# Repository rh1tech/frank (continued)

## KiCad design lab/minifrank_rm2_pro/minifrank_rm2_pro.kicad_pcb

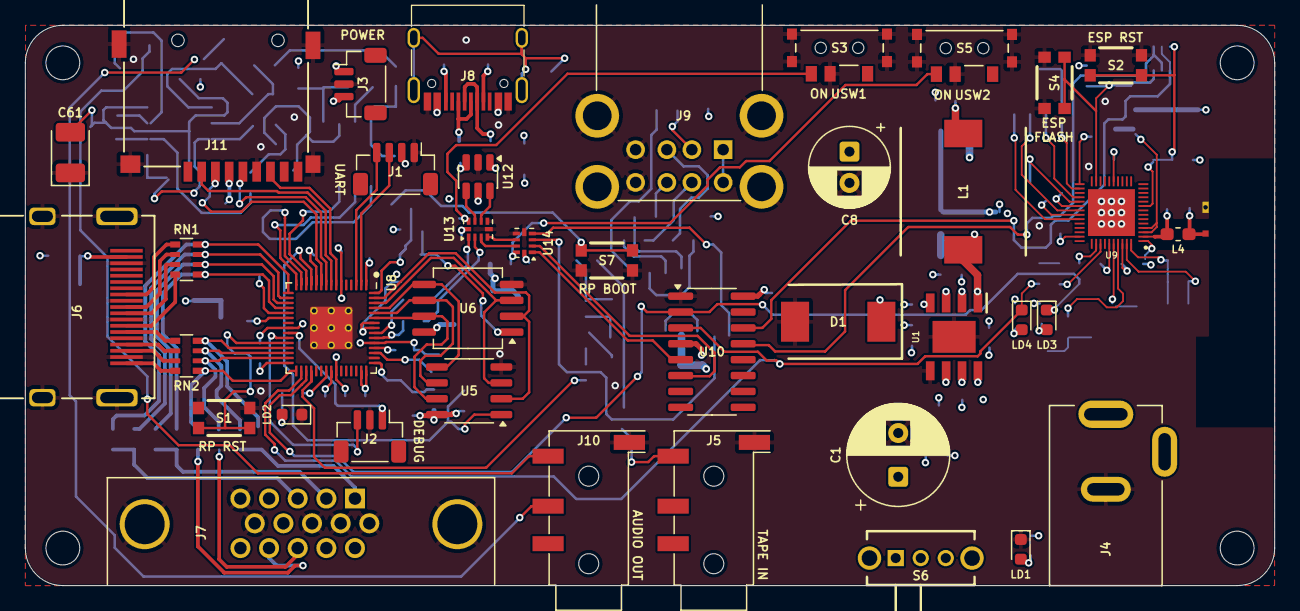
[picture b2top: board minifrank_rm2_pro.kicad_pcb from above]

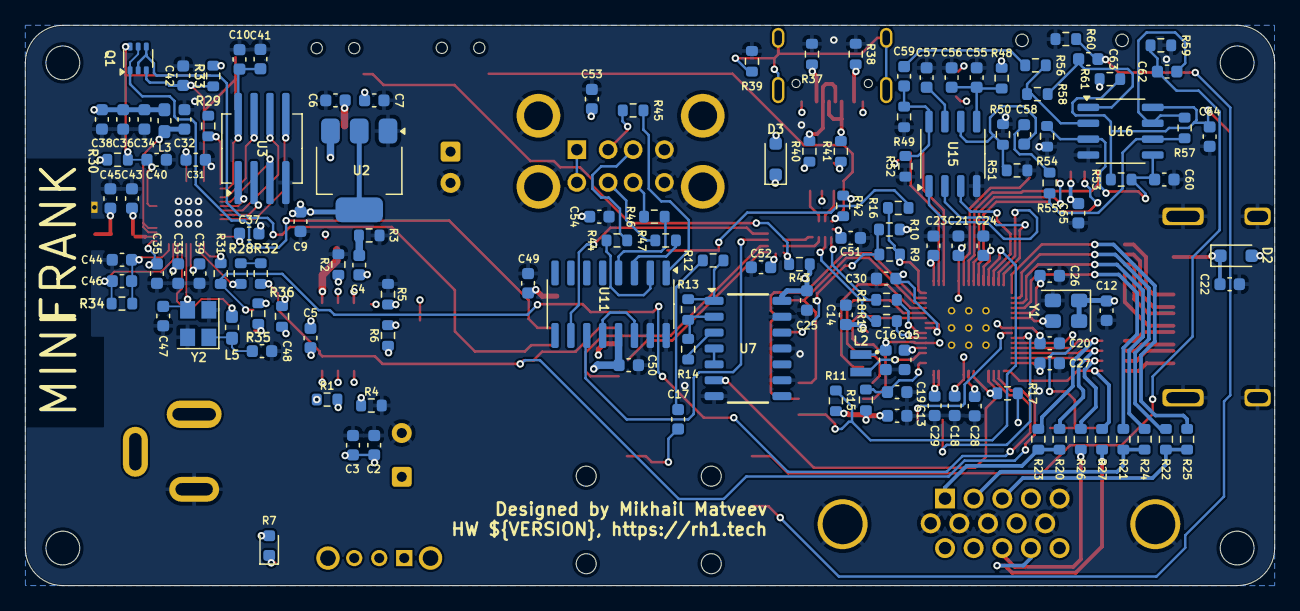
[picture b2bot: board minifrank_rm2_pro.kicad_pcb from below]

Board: 4 copper layers, 99.9 x 44.8 mm, 179 parts (135 on the bottom side), 141 nets.

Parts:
AE1: Antenna_Shield; Antenna (2.4GHz)
C1: 680u; Capacitor (Radial_D8.0mm_P3.50mm)
C2, C7, C9, C36, C53, C54, C55, C57, C58, C59, C60, C62, C63: 10u; C_0603_1608Metric
C3, C5, C6, C10, C12, C13, C14, C17, C18, C21, C22, C23, C24, C25, C26, C27, C28, C29, C30, C32, C34, C35, C37, C39, C49, C51, C52, C56, C64, C65: 100n; C_0603_1608Metric
C4: 150pF; C_0603_1608Metric
C8: 220u; Capacitor (Radial_D6.3mm_P2.50mm)
C15, C16, C19, C20, C50: 4.7u; C_0603_1608Metric
C31, C38, C41: 1u; C_0603_1608Metric
C33: 100p; C_0603_1608Metric
C40, C42: 1n; C_0603_1608Metric
C43: 1.5pF; C_0603_1608Metric
C44: 10n; C_0603_1608Metric
C45: 2.4pF; C_0603_1608Metric
C46: 3.3n; C_0603_1608Metric
C47, C48: 12p; C_0603_1608Metric
C61: 10u; Capacitor (3528, tantalum, polar)
D1: 1N5822; SS34
D2, D3: 1N5819WS; Diode (SOD-323)
H1, H2, H3, H4: Hole 2.7mm; Mounting Hole (2.7mm)
J1: UART; JST_SH_BM04B-SRSS-TB_1x04-1MP_P1.00mm_Vertical
J2: DEBUG; JST_SH_BM03B-SRSS-TB_1x03-1MP_P1.00mm_Vertical
J3: PWR; JST_SH_BM03B-SRSS-TB_1x03-1MP_P1.00mm_Vertical
J4: DC-005-5A-2.0; XKB_DC-005-5A-2.0
J5, J10: PJ-320D; Jack (3.5mm, PJ-320D)
J6: DC3RX19JA2; HDMI (female)
J7: VGA; D-SUB (15 pin, female)
J8: USB4215-03-A; USB Type C
J9: SS-52100-004; USB Type A (stacked)
J11: 104031-0811; MicroSD (SMD, long)
L1: 22uH; CDRH104RNP
L2: 3.3u; L_pol_2016
L3: 2nH; Inductor (0603 1.05x0.95)
L4: 2.7nH/0R; Inductor (0603 1.05x0.95)
L5: 24nH/0R; Inductor (0603 1.05x0.95)
LD1: Power; LED_0603_1608Metric
LD2: Blue; LED_0603_1608Metric
LD3, LD4: Orange; LED_0603_1608Metric
Q1: UMH3N; SOT-363
R1, R3, R4, R13, R14: 100K; R_0603_1608Metric
R2: 24K; R_0603_1608Metric
R5: 8.2K; R_0603_1608Metric
R6: 43K; R_0603_1608Metric
R7: 1K; LED_0603_1608Metric
R9: 0R; R_0603_1608Metric
R10, R11, R42, R43, R51, R52, R53, R54, R55, R56: 10K; R_0603_1608Metric
R12: 4.7K; R_0603_1608Metric
R15: 33R; R_0603_1608Metric
R16, R17, R23, R24, R25: 1K; R_0603_1608Metric
R18, R19: 27R; R_0603_1608Metric
R20, R21, R22: 330R; R_0603_1608Metric
R26, R27, R48, R61: 100R; R_0603_1608Metric
R28: 499R; Resistor (0603, S)
R29: 0R; Resistor (0603, S)
R30, R33: 10K; Resistor (0603, S)
R31, R32: 330R; Resistor (0603, S)
R34: 20K; Resistor (0603, S)
R35, R36: 1.5K; Resistor (0603, S)
R37, R38: 5.1K; R_0603_1608Metric
R39: 1M; R_0603_1608Metric
R40, R41, R44, R45, R46, R47: 22R; R_0603_1608Metric
R49, R50: 470R; R_0603_1608Metric
R57, R58: 47K; R_0603_1608Metric
R59, R60: 20K; R_0603_1608Metric
RN1, RN2: 270R; Resistor Array (4x0603)
S1: RP Reset; KMR_2
S2: ESP Reset; KMR_2
S3, S5: MSK12C02; SW_MSK12C02
S4: ESP Flash; KMR_2
S6: SK12D07VG3NS
S7: RP Flash; KMR_2
U1: MP1584EN-LF-Z; SOIC127P600X170-9N
U2: AMS1117 3.3; SOT-223
U3: W25Q32JVSIQ; SOIC-8 (Longer)
U5: ESP-PSRAM32; SO-8
U6: W25Q128JVS; SOIC-8
U7: CD4069UBM; SOIC127P600X175-14N
U8: RP2350; QFN 60 (RP2350A)
U9: ESP32-D0WD-V3; QFN35P500X500X90-49N-D
U10: CH340C; SOP-16
U11: MW7211A; SOP-16
U12: USBLC6-2SC6; SOT-23-6
U13, U14: TS3USB221RSER; UQFN-10
U15: TDA1387T; SO-8
U16: LM358; SO-8
Y1: ASE-12MHz; Oscillator_SMD_Abracon_ASE-4Pin_3.2x2.5mm
Y2: 40MHz; Crystal (3225)

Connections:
+1V1: C16.1, C18.1, C20.1, C21.1, L2.1, U8.6 (DVDD), U8.23 (DVDD), U8.39 (DVDD), U8.50 (VREG_FB)
+3.3VP: C32.1, L3.2, U9.3 (VDD3P3_1), U9.4 (VDD3P3_2)
+3V3: C9.1, C12.1, C13.1, C14.1, C15.1, C23.1, C24.1, C25.1, C26.1, C27.1, C28.1, C29.1, C30.1, C31.1, C33.1, C34.1, C35.1, C36.1, C37.1, C38.1, C39.1, C49.1, C51.2, C52.2, C65.2, J1.2, J3.1, J11.4 (VDD), L3.1, R7.2, R10.1, R11.2, R15.1, R30.2, R33.2, R35.2, R36.1, R42.1, R43.1, U2.2 (VO), U5.8 (VCC), U6.8 (VCC), U7.14 (VDD), U8.1 (IOVDD), U8.11 (IOVDD), U8.20 (IOVDD), U8.30 (IOVDD), U8.38 (IOVDD), U8.44 (ADC_AVDD), U8.45 (IOVDD), U8.49 (VREG_VIN), U8.53 (USB_OTP_VDD), U8.54 (QSPI_IOVDD), U9.1 (VDDA_1), U9.19 (VDD3P3_RTC), U9.37 (VDD3P3_CPU), U9.43 (VDDA_2), U9.46 (VDDA_3), U10.4 (3V), U10.16 (VCC), U13.10 (VCC), U14.10 (VCC), Y1.1 (EN), Y1.4 (Vdd)
/Audio/AMP_OUTL: C62.2, J10.T, R59.2
/Audio/AMP_OUTR: C63.2, J10.R, R60.2
/Audio/TDA_L: C58.1, R50.2, R51.1, U15.6 (A_LEFT)
/Audio/TDA_R: C59.1, R49.1, R52.1, U15.8 (A_RIGHT)
/ESP32/ANT: AE1.1 (A), C45.1, L4.1
/ESP32/CAP1: C44.1, C46.1, R34.2, U9.48 (CAP1)
/ESP32/CAP2: C46.2, R34.1, U9.47 (CAP2)
/ESP32/LNA_IN: C43.1, L4.2, U9.2 (LNA_IN)
/ESP32/U0RXD: R31.2, U9.40 (U0RXD)
/ESP32/U0TXD: R28.2, R32.2
/ESP32/XTAL_N: C47.1, U9.44 (XTAL_N), Y2.3
/ESP32/XTAL_P: L5.1, U9.45 (XTAL_P)
/ESP_CHIP_PU: C40.1, Q1.6 (C1), R30.1, S2.2, S2.4, U9.9 (CHIP_PU)
/ESP_DTR: Q1.2 (B1), Q1.4 (E2), U10.13 (DTR)
/ESP_GPIO0: C42.1, Q1.3 (C2), R33.1, S4.2, S4.4, U9.23 (GPIO0)
/ESP_RTS: Q1.1 (E1), Q1.5 (B2), U10.14 (RTS)
/ESP_RXD: LD3.1 (K), R31.1, U8.33 (GPIO21), U10.2 (TxD)
/ESP_SCK/CLK: U3.6 (CLK), U9.31 (SD_CLK)
/ESP_SCS/CMD: U3.1 (~CS), U9.30 (SD_CMD)
/ESP_SDI/SD1: U3.5 (DI(IO0)), U9.33 (SD_DATA_1)
/ESP_SDO/SD0: U3.2 (DO(IO1)), U9.32 (SD_DATA_0)
/ESP_SHD/SD2: U3.7 (IO3), U9.28 (SD_DATA_2)
/ESP_SWP/SD3: U3.3 (IO2), U9.29 (SD_DATA_3)
/ESP_TXD: LD4.1 (K), R32.1, U8.32 (GPIO20), U10.3 (RxD)
/GPIO0: J1.3, U8.2 (GPIO0)
/GPIO1: J1.4, U8.3 (GPIO1)
/GPIO4: J11.7 (DAT0), U8.7 (GPIO4)
/GPIO5: J11.2 (DAT3/CD), U8.8 (GPIO5)
/GPIO6: J11.5 (CLK), U8.9 (GPIO6)
/GPIO7: J11.3 (CMD), U8.10 (GPIO7)
/GPIO8: R11.1, U5.1 (~CE), U8.12 (GPIO8)
/GPIO9: U8.13 (GPIO9), U15.3 (DATA)
/GPIO10: U8.14 (GPIO10), U15.1 (SCLK)
/GPIO11: U8.15 (GPIO11), U15.2 (LRCK)
/GPIO12: R25.1, RN1.4 (R4.1), U8.16 (GPIO12)
/GPIO13: R22.1, RN1.3 (R3.1), U8.17 (GPIO13)
/GPIO14: R24.1, RN1.2 (R2.1), U8.18 (GPIO14)
/GPIO15: R21.1, RN1.1 (R1.1), U8.19 (GPIO15)
/GPIO16: R23.1, RN2.4 (R4.1), U8.27 (GPIO16)
/GPIO17: R20.1, RN2.3 (R3.1), U8.28 (GPIO17)
/GPIO18: R26.2, RN2.2 (R2.1), U8.29 (GPIO18)
/GPIO19: R27.2, RN2.1 (R1.1), U8.31 (GPIO19)
/GPIO22: U7.6 (I=*C), U8.34 (GPIO22)
/Power/VBUS_CON: J4.1, S6.2
/Power/VBUS_IN: C1.1, C2.1, C3.1, R1.2, S6.1, U1.7 (VIN)
/RP2350A/FLASH_SS: R9.2, R10.2, U6.1 (~CS)
/RP2350A/QSPI_SCLK: U5.6 (SCLK), U6.6 (CLK), U8.56 (QSPI_SCLK)
/RP2350A/QSPI_SD0: U5.5 (SI/SIO), U6.5 (DI(IO0)), U8.57 (QSPI_SD0)
/RP2350A/QSPI_SD1: U5.2 (SO/SIO), U6.2 (DO(IO1)), U8.59 (QSPI_SD1)
/RP2350A/QSPI_SD2: U5.3 (SIO2), U6.3 (IO2), U8.58 (QSPI_SD2)
/RP2350A/QSPI_SD3: U5.7 (SIO3), U6.7 (IO3), U8.55 (QSPI_SD3)
/RP2350A/QSPI_SS: R9.1, R16.1, U8.60 (QSPI_SS)
/RP2350A/VREG_AVDD: C19.1, R15.2, U8.46 (VREG_AVDD)
/RP2350A/VREG_LX: L2.2, U8.48 (VREG_LX)
/RP2350A/XIN: U8.21 (XIN), Y1.3 (OUT)
/RP2350A/~USB_BOOT: R16.2, S7.2, S7.4
/RP_D+: R18.1, U13.1 (1D+)
/RP_D-: R19.1, U13.2 (1D-)
/RUN: S1.2, S1.4, U8.26 (RUN)
/SWCLK: J2.1, U8.24 (SWCLK)
/SWD: J2.3, U8.25 (SWD)
/Tape In/TAPE: C17.2, J5.T
/UC_D+: U12.4 (I/O2), U13.8 (D+)
/UC_D-: U12.6 (I/O1), U13.7 (D-)
/UH_D+: U11.11 (DPU), U14.3 (2D+)
/UH_D-: U11.10 (DMU), U14.4 (2D-)
/USB Multiplexers/M1D2+: U13.3 (2D+), U14.8 (D+)
/USB Multiplexers/M1D2-: U13.4 (2D-), U14.7 (D-)
/USB/DS1+: R44.1, U11.2 (DP0)
/USB/DS1-: R45.1, U11.1 (DM0)
/USB/DS2+: R46.1, U11.4 (DP1)
/USB/DS2-: R47.1, U11.3 (DM1)
/USW1: R42.2, S3.3, U13.9 (S)
/USW2: R43.2, S5.3, U14.9 (S)
/UT_D+: U10.5 (D+), U14.1 (1D+)
/UT_D-: U10.6 (D-), U14.2 (1D-)
/VDD_SDIO: C10.1, C41.1, U3.8 (VCC), U9.26 (VDD_SDIO)
GND: AE1.2 (Shield), C1.2, C2.2, C3.2, C6.1, C7.2, C8.2, C9.2, C10.2, C12.2, C13.2, C14.2, C15.2, C16.2, C18.2, C19.2, C20.2, C21.2, C22.2, C23.2, C24.2, C25.2, C26.2, C27.2, C28.2, C29.2, C30.2, C31.2, C32.2, C33.2, C34.2, C35.2, C36.2, C37.2, C38.2, C39.2, C40.2, C41.2, C42.2, C43.2, C44.2, C45.2, C47.2, C48.2, C49.2, C50.2, C51.1, C52.1, C53.2, C54.2, C55.2, C56.2, C57.2, C60.1, C61.1, C64.1, C65.1, D1.2 (A), J1.1, J2.2, J3.2, J4.2, J5.S, J6.2 (G_D2), J6.5 (G_D1), J6.8 (G_D0), J6.11 (G_CLK), J6.17 (G_DDC/CEC), J6.20 (SHIELD1), J6.21 (SHIELD2), J6.22 (SHIELD3), J6.23 (SHIELD4), J7.0, J7.5, J7.6, J7.7, J7.8, J7.10, J8.1 (GND), J8.12 (GND), J9.4 (GND1), J9.8 (GND2), J9.9 (Shield), J10.S, J11.6 (VSS), LD1.1 (K), LD2.1 (K), R2.2, R3.2, R4.2, R5.1, R37.1, R38.1, R39.2, R49.2, R50.1, R51.2, R52.2, R54.1, R59.1, R60.1, S1.1, S1.3, S2.1, S2.3, S3.2, S3.4_1 (GND), S3.4_2 (GND), S3.4_3 (GND), S3.4_4 (GND), S4.1, S4.3, S5.2, S5.4_1 (GND), S5.4_2 (GND), S5.4_3 (GND), S5.4_4 (GND), S7.1, S7.3, U1.5 (GND), U1.9 (EP), U2.1 (GND), U3.4 (GND), U5.4 (VSS), U6.4 (GND), U7.7 (VSS), U7.9 (D14), U7.11 (E), U7.13 (F), U8.47 (VREG_PGND), U8.61 (GND), U9.49 (GND), U10.1 (GND), U11.15 (GND), U11.16 (GND), U12.2 (GND), U13.5 (GND), U13.6 (~OE), U14.5 (GND), U14.6 (~OE), U15.4 (AGND), U16.4 (V-), Y1.2 (GND), Y2.2 (G), Y2.4 (G)
GPIO25: R17.2, U8.37 (GPIO25)
unnamed: C4.2, R3.1
unnamed: C17.1, R12.2
unnamed: C48.1, L5.2, Y2.1
unnamed: C58.2, R55.2
unnamed: C59.2, R56.2
unnamed: C62.1, R57.1, U16.7
unnamed: C63.1, R58.1, U16.1
unnamed: C5.2, D1.1 (K), L1.1, U1.1 (SW)
unnamed: C22.1, D2.1 (K), J6.18 (+5V)
unnamed: D3.2 (A), J8.2 (VBUS), J8.11 (VBUS)
unnamed: J6.12 (CLKN), RN1.5 (R4.2)
unnamed: J6.10 (CLKP), RN1.6 (R3.2)
unnamed: J6.9 (D0N), RN1.7 (R2.2)
unnamed: J6.7 (D0P), RN1.8 (R1.2)
unnamed: J6.6 (D1N), RN2.5 (R4.2)
unnamed: J6.4 (D1P), RN2.6 (R3.2)
unnamed: J6.3 (D2N), RN2.7 (R2.2)
unnamed: J6.1 (D2P), RN2.8 (R1.2)
unnamed: J7.1, R20.2, R23.2
unnamed: J7.2, R21.2, R24.2
unnamed: J7.3, R22.2, R25.2
unnamed: J7.13, R26.1
unnamed: J7.14, R27.1
unnamed: J8.4 (CC1), R37.2
unnamed: J8.10 (CC2), R38.2
unnamed: J8.5 (DN2), J8.7 (DN1), R40.2
unnamed: J8.6 (DP1), J8.8 (DP2), R41.2
unnamed: J8.13 (SHIELD), R39.1
unnamed: J9.3 (D1+), R44.2
unnamed: J9.2 (D1-), R45.2
unnamed: J9.7 (D2+), R46.2
unnamed: J9.6 (D2-), R47.2
unnamed: LD1.2 (A), R7.1
unnamed: LD2.2 (A), R17.1
unnamed: LD3.2 (A), R35.1
unnamed: LD4.2 (A), R36.2
unnamed: R40.1, U12.1 (I/O1)
unnamed: R41.1, U12.3 (I/O2)
unnamed: C5.1, U1.8 (BST)
unnamed: C4.1, U1.3 (COMP)
unnamed: R1.1, R2.1, U1.2 (EN)
unnamed: R5.2, R6.2, U1.4 (FB)
unnamed: R4.1, U1.6 (FREQ)
unnamed: R12.1, R13.2, U7.1 (A)
unnamed: R14.1, U7.3 (B)
unnamed: U7.4 (H=*B), U7.5 (C)
unnamed: R13.1, R14.2, U7.2 (G-*A)
unnamed: R19.2, U8.51 (USB_DM)
unnamed: R18.2, U8.52 (USB_DP)
unnamed: R29.1, U9.25 (GPIO16)
unnamed: R28.1, U9.41 (U0TXD)
unnamed: U11.12 (VD33), U11.14 (VD3)
unnamed: C57.1, U15.7 (FLT)
unnamed: C55.1, C56.1, R48.1, U15.5 (VA)
unnamed: C60.2, R53.1, R54.2, U16.3 (+), U16.5 (+)
unnamed: R56.1, R58.2, U16.2 (-)
unnamed: R55.1, R57.2, U16.6 (-)
unnamed: C61.2, C64.2, R53.2, R61.2, U16.8 (V+)
VBUS: C6.2, C7.1, C8.1, C50.1, C53.1, C54.1, D2.2 (A), D3.1 (K), J3.3, J9.1 (VBUS1), J9.5 (VBUS2), L1.2, R6.1, R48.2, R61.1, U2.3 (VI), U11.13 (VDD5), U12.5 (VBUS)

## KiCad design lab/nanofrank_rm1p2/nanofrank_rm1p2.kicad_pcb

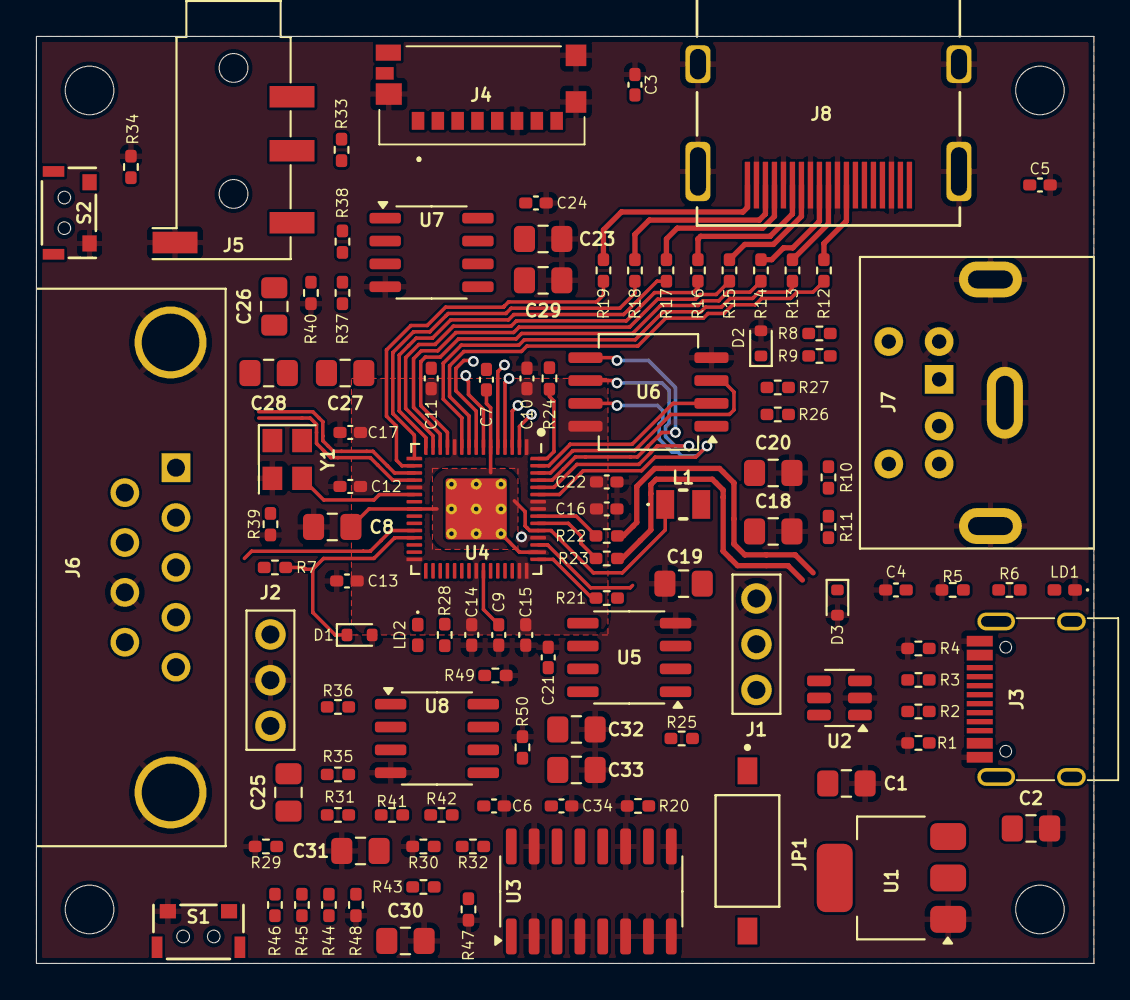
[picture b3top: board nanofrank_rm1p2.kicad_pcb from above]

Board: 4 copper layers, 58.8 x 51.5 mm, 114 parts (0 on the bottom side), 83 nets.

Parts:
C1, C2, C23, C25, C26, C27, C28, C29, C32, C33: 10u; Capacitor (0805)
C3, C4, C5, C6, C7, C9, C10, C11, C12, C13, C14, C15, C16, C17, C21, C22, C24, C34: 100n; Capacitor (0402)
C8, C18, C19, C20: 4.7u; Capacitor (0805)
C30, C31: 47n; Capacitor (0805)
D1, D2, D3: 3V3; Diode (SOD-523)
H1, H2, H3, H4: MountingHole; Mounting Hole (2.7mm)
J1: UART; Pin Header (1x03)
J2: PWR; Pin Header (1x03)
J3: USB4215-03-A; USB Type C
J4: 0475710001; MicroSD (SMD, short)
J5: PJ-320D; Jack (3.5mm, PJ-320D)
J6: D-SUB 9 Male; D-SUB (9 pin, male, top mount)
J7: MDC-036; MiniDIN (6 Pin, female)
J8: DC3RX19JA2; HDMI (female)
JP1: Main Jumpers; SW_DS04-254-2-01BK-SMT
L1: 3.3u; Inductor (0806)
LD1: Power; LED (0402)
LD2: Blue; LED (0402)
R1, R4: 5.1K; Resistor (0402)
R2, R3: 22R; Resistor (0402)
R5: 1M; Resistor (0402)
R6, R7, R8, R11, R24, R28, R45, R46: 1K; Resistor (0402)
R9, R10: 100R; Resistor (0402)
R12, R13, R14, R15, R16, R17, R18, R19: 270R; Resistor (0402)
R20, R25, R26, R31, R32, R33, R35, R37, R40, R43, R44: 10K; Resistor (0402)
R21: 33R; Resistor (0402)
R22, R23: 27R; Resistor (0402)
R27: 0R; Resistor (0402)
R29, R30, R41, R42, R47, R48: 2K; Resistor (0402)
R34, R39: 20K; Resistor (0402)
R36, R38: 47K; Resistor (0402)
R49, R50: 470R; Resistor (0402)
S1: Reset; TACT-SIDE-4623
S2: TS-1233; TACT-SIDE-4623
U1: NCP1117 3.3; SOT-223
U2: USBLC6-2SC6; SOT-23-6
U3: 74HC4052D; SOP-16
U4: RP2350; QFN 60 (RP2350A)
U5: ESP-PSRAM32; SO-8
U6: W25Q128JVS; SOIC-8
U7: LM358; SO-8
U8: TDA1387T; SO-8
Y1: ASE-12MHz; Crystal (3225, active)

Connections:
+1V1: C7.1, C8.1, C9.1, C20.1, L1.1, U4.6 (DVDD), U4.23 (DVDD), U4.39 (DVDD), U4.50 (VREG_FB)
+3V3: C1.1, C3.2, C6.2, C10.1, C11.1, C12.1, C13.1, C14.1, C15.1, C16.1, C17.1, C19.1, C21.1, C22.1, J2.1, J4.P4 (VDD), JP1.2, R6.2, R21.1, R25.2, R26.1, U1.2 (VO), U3.16 (VCC), U4.1 (IOVDD), U4.11 (IOVDD), U4.20 (IOVDD), U4.30 (IOVDD), U4.38 (IOVDD), U4.44 (ADC_AVDD), U4.45 (IOVDD), U4.49 (VREG_VIN), U4.53 (USB_OTP_VDD), U4.54 (QSPI_IOVDD), U5.8 (VCC), U6.8 (VCC), Y1.1 (EN), Y1.4 (Vdd)
/AMP_IN_L: C25.1, R31.1, U3.13 (1Z)
/AMP_IN_R: C27.1, R32.1, U3.3 (2Z)
/AUDIOSW: JP1.1, R20.2, U3.10 (S0)
/Audio Out/AMP_OUTL: C26.2, J5.T, R34.2
/Audio Out/AMP_OUTR: C28.2, J5.R, R39.2
/GPIO0: D2.1 (K), J1.2, R9.2, U4.2 (GPIO0)
/GPIO1: D3.1 (K), J1.3, R10.2, U4.3 (GPIO1)
/GPIO2: J4.P5 (CLK), U4.4 (GPIO2)
/GPIO3: J4.P3 (CMD), U4.5 (GPIO3)
/GPIO4: J4.P7 (DAT0), U4.7 (GPIO4)
/GPIO5: J4.P2 (CD/DAT3), U4.8 (GPIO5)
/GPIO6: R12.2, U4.9 (GPIO6)
/GPIO7: R13.2, U4.10 (GPIO7)
/GPIO8: R14.2, U4.12 (GPIO8)
/GPIO9: R15.2, U4.13 (GPIO9)
/GPIO10: R16.2, U4.14 (GPIO10)
/GPIO11: R17.2, U4.15 (GPIO11)
/GPIO12: R18.2, U4.16 (GPIO12)
/GPIO13: R19.2, U4.17 (GPIO13)
/GPIO14: J6.4, U4.18 (GPIO14)
/GPIO15: J6.3, U4.19 (GPIO15)
/GPIO16: D1.1 (K), R7.1, U4.27 (GPIO16)
/GPIO19: R25.1, U4.31 (GPIO19), U5.1 (~CE)
/GPIO26: R46.2, U4.40 (GPIO26_ADC0), U8.3 (DATA)
/GPIO27: R45.2, U4.41 (GPIO27_ADC1), U8.1 (SCLK)
/GPIO28: R41.1, R42.1, U4.42 (GPIO28_ADC2), U8.2 (LRCK)
/KB_CLK: J7.5, R8.2, R9.1
/KB_DATA: J7.1, R10.1, R11.2
/PWM_OUT_L: R44.2, R48.1, U3.12 (1Y0)
/PWM_OUT_R: R43.2, R47.1, U3.1 (2Y0)
/PW_D+: R22.1, U2.4 (I/O2)
/PW_D-: R23.1, U2.6 (I/O1)
/RP2350A/FLASH_SS: R26.2, R27.2, U6.1 (~CS)
/RP2350A/QSPI_SCLK: U4.56 (QSPI_SCLK), U5.6 (SCLK), U6.6 (CLK)
/RP2350A/QSPI_SD0: U4.57 (QSPI_SD0), U5.5 (SI/SIO), U6.5 (DI(IO0))
/RP2350A/QSPI_SD1: U4.59 (QSPI_SD1), U5.2 (SO/SIO), U6.2 (DO(IO1))
/RP2350A/QSPI_SD2: U4.58 (QSPI_SD2), U5.3 (SIO2), U6.3 (IO2)
/RP2350A/QSPI_SD3: U4.55 (QSPI_SD3), U5.7 (SIO3), U6.7 (IO3)
/RP2350A/QSPI_SS: R24.1, R27.1, U4.60 (QSPI_SS)
/RP2350A/VREG_AVDD: C18.1, R21.2, U4.46 (VREG_AVDD)
/RP2350A/VREG_LX: L1.2, U4.48 (VREG_LX)
/RP2350A/XIN: U4.21 (XIN), Y1.3 (OUT)
/RP2350A/~USB_BOOT: R24.2, S2.2
/RUN: S1.1, U4.26 (RUN)
/TDA_L: R50.2, U3.14 (1Y1), U8.6 (A_LEFT)
/TDA_R: R49.1, U3.5 (2Y1), U8.8 (A_RIGHT)
GND: C1.2, C2.2, C3.1, C4.2, C5.2, C6.1, C7.2, C8.2, C9.2, C10.2, C11.2, C12.2, C13.2, C14.2, C15.2, C16.2, C17.2, C18.2, C19.2, C20.2, C21.2, C22.2, C23.1, C24.1, C29.1, C30.2, C31.2, C32.2, C33.2, C34.2, D1.2 (A), D2.2 (A), D3.2 (A), J1.1, J2.2, J3.1 (GND), J3.12 (GND), J4.G1 (GND_1), J4.G2 (GND_2), J4.G3 (GND_3), J4.P6 (VSS), J5.S, J6.8, J7.3, J8.2 (G_D2), J8.5 (G_D1), J8.8 (G_D0), J8.11 (G_CLK), J8.17 (G_DDC/CEC), J8.20 (SHIELD1), J8.21 (SHIELD2), J8.22 (SHIELD3), J8.23 (SHIELD4), LD1.1 (K), LD2.1 (K), R1.1, R4.1, R5.2, R20.1, R29.2, R30.2, R34.1, R39.1, R40.1, R47.2, R48.2, R49.2, R50.1, S1.2, S2.1, U1.1 (GND), U2.2 (GND), U3.2 (2Y2), U3.4 (2Y3), U3.6 (~E), U3.7 (VEE), U3.8 (GND), U3.9 (S1), U3.11 (1Y3), U3.15 (1Y2), U4.47 (VREG_PGND), U4.61 (GND), U5.4 (VSS), U6.4 (GND), U7.4 (V-), U8.4 (AGND), Y1.2 (GND)
GPIO25: R28.2, U4.37 (GPIO25)
unnamed: C25.2, R35.2
unnamed: C26.1, R36.1, U7.7
unnamed: C27.2, R37.2
unnamed: C28.1, R38.1, U7.1
unnamed: C30.1, R41.2, R43.1, R46.1
unnamed: C31.1, R42.2, R44.1, R45.1
unnamed: J3.4 (CC1), R1.2
unnamed: J3.10 (CC2), R4.2
unnamed: J3.5 (DN2), J3.7 (DN1), R2.2
unnamed: J3.6 (DP1), J3.8 (DP2), R3.2
unnamed: J3.13 (SHIELD), R5.1
unnamed: J6.2, R7.2
unnamed: J8.12 (CLKN), R12.1
unnamed: J8.10 (CLKP), R13.1
unnamed: J8.9 (D0N), R14.1
unnamed: J8.7 (D0P), R15.1
unnamed: J8.6 (D1N), R16.1
unnamed: J8.4 (D1P), R17.1
unnamed: J8.3 (D2N), R18.1
unnamed: J8.1 (D2P), R19.1
unnamed: LD1.2 (A), R6.1
unnamed: LD2.2 (A), R28.1
unnamed: R2.1, U2.1 (I/O1)
unnamed: R3.1, U2.3 (I/O2)
unnamed: R29.1, R31.2
unnamed: R30.1, R32.2
unnamed: R23.2, U4.51 (USB_DM)
unnamed: R22.2, U4.52 (USB_DP)
unnamed: C29.2, R33.1, R40.2, U7.3 (+), U7.5 (+)
unnamed: R37.1, R38.2, U7.2 (-)
unnamed: R35.1, R36.2, U7.6 (-)
unnamed: C32.1, U8.7 (FLT)
VBUS: C2.1, C4.1, C5.1, C23.2, C24.2, C33.1, C34.1, J2.3, J3.2 (VBUS), J3.11 (VBUS), J6.6, J7.4, J8.18 (+5V), R8.1, R11.1, R33.2, U1.3 (VI), U2.5 (VBUS), U7.8 (V+), U8.5 (VA)

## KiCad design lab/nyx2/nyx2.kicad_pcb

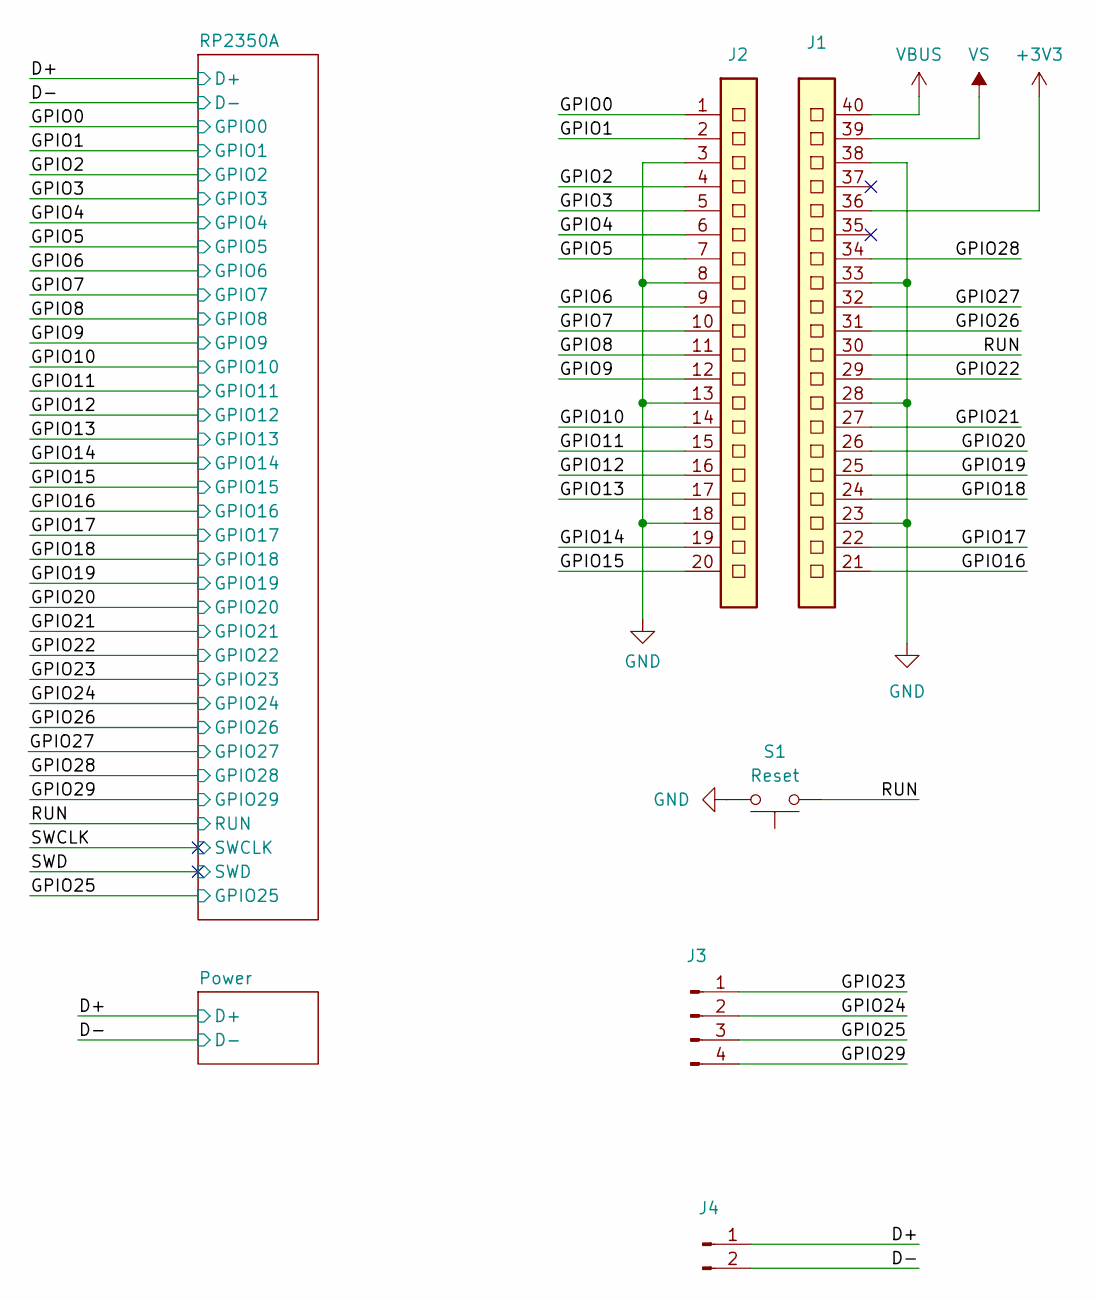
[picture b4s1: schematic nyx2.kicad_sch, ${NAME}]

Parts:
J1: CON_PICO_21-40
J2: CON_PICO_1-20
J3: Test Points (1mm x 5)
J4: Test Points (1mm x 2)
S1: Reset; Button (SMD, 3x3mm, 1-1)

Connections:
+3V3: J1.36; also elsewhere on the board
/D+: J4.1; also elsewhere on the board
/D-: J4.2; also elsewhere on the board
/GPIO0: J2.1; also elsewhere on the board
/GPIO1: J2.2; also elsewhere on the board
/GPIO2: J2.4; also elsewhere on the board
/GPIO3: J2.5; also elsewhere on the board
/GPIO4: J2.6; also elsewhere on the board
/GPIO5: J2.7; also elsewhere on the board
/GPIO6: J2.9; also elsewhere on the board
/GPIO7: J2.10; also elsewhere on the board
/GPIO8: J2.11; also elsewhere on the board
/GPIO9: J2.12; also elsewhere on the board
/GPIO10: J2.14; also elsewhere on the board
/GPIO11: J2.15; also elsewhere on the board
/GPIO12: J2.16; also elsewhere on the board
/GPIO13: J2.17; also elsewhere on the board
/GPIO14: J2.19; also elsewhere on the board
/GPIO15: J2.20; also elsewhere on the board
/GPIO16: J1.21; also elsewhere on the board
/GPIO17: J1.22; also elsewhere on the board
/GPIO18: J1.24; also elsewhere on the board
/GPIO19: J1.25; also elsewhere on the board
/GPIO20: J1.26; also elsewhere on the board
/GPIO21: J1.27; also elsewhere on the board
/GPIO22: J1.29; also elsewhere on the board
/GPIO23: J3.1; also elsewhere on the board
/GPIO24: J3.2; also elsewhere on the board
/GPIO26: J1.31; also elsewhere on the board
/GPIO27: J1.32; also elsewhere on the board
/GPIO28: J1.34; also elsewhere on the board
/GPIO29: J3.4; also elsewhere on the board
/RUN: J1.30, S1.1; also elsewhere on the board
GND: J1.23, J1.28, J1.33, J1.38, J2.3, J2.8, J2.13, J2.18, S1.2; also elsewhere on the board
GPIO25: J3.3; also elsewhere on the board
VBUS: J1.40; also elsewhere on the board
VS: J1.39

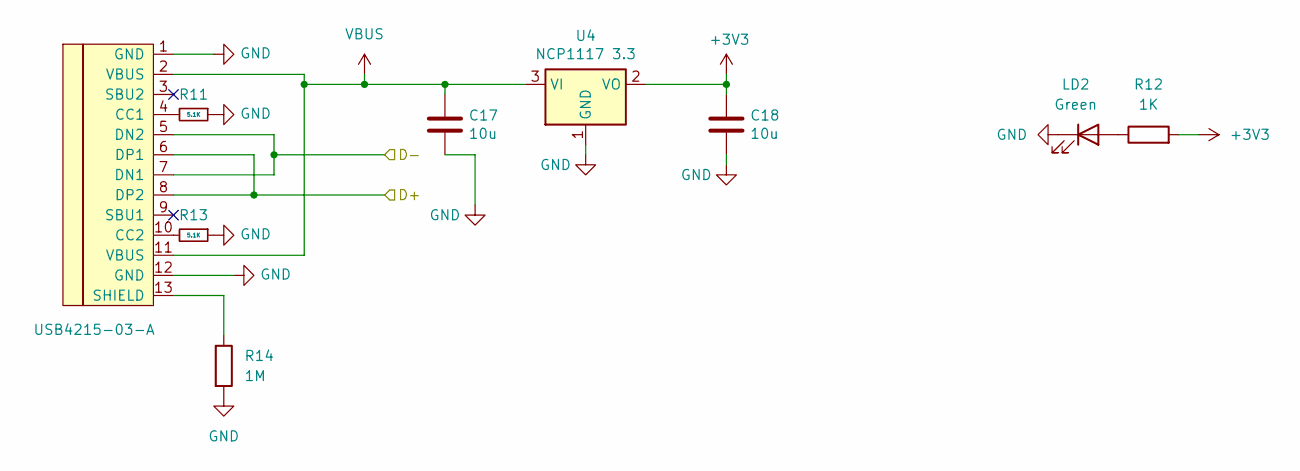
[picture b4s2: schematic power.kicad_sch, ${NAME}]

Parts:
C17, C18: 10u; Capacitor (0805)
J5: USB4215-03-A; USB Type C
LD2: Green; LED (0402)
R11, R13: 5.1K; Resistor (0402)
R12: 1K; Resistor (0402)
R14: 1M; Resistor (0402)
U4: NCP1117 3.3; SOT-223

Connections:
+3V3: C18.1, R12.2, U4.2 (VO); also elsewhere on the board
/D+: J5.6 (DP1), J5.8 (DP2); also elsewhere on the board
/D-: J5.5 (DN2), J5.7 (DN1); also elsewhere on the board
GND: C17.2, C18.2, J5.1 (GND), J5.12 (GND), LD2.1 (K), R11.1, R13.1, R14.2, U4.1 (GND); also elsewhere on the board
unnamed: J5.4 (CC1), R11.2
unnamed: J5.10 (CC2), R13.2
unnamed: J5.13 (SHIELD), R14.1
unnamed: LD2.2 (A), R12.1
VBUS: C17.1, J5.2 (VBUS), J5.11 (VBUS), U4.3 (VI); also elsewhere on the board

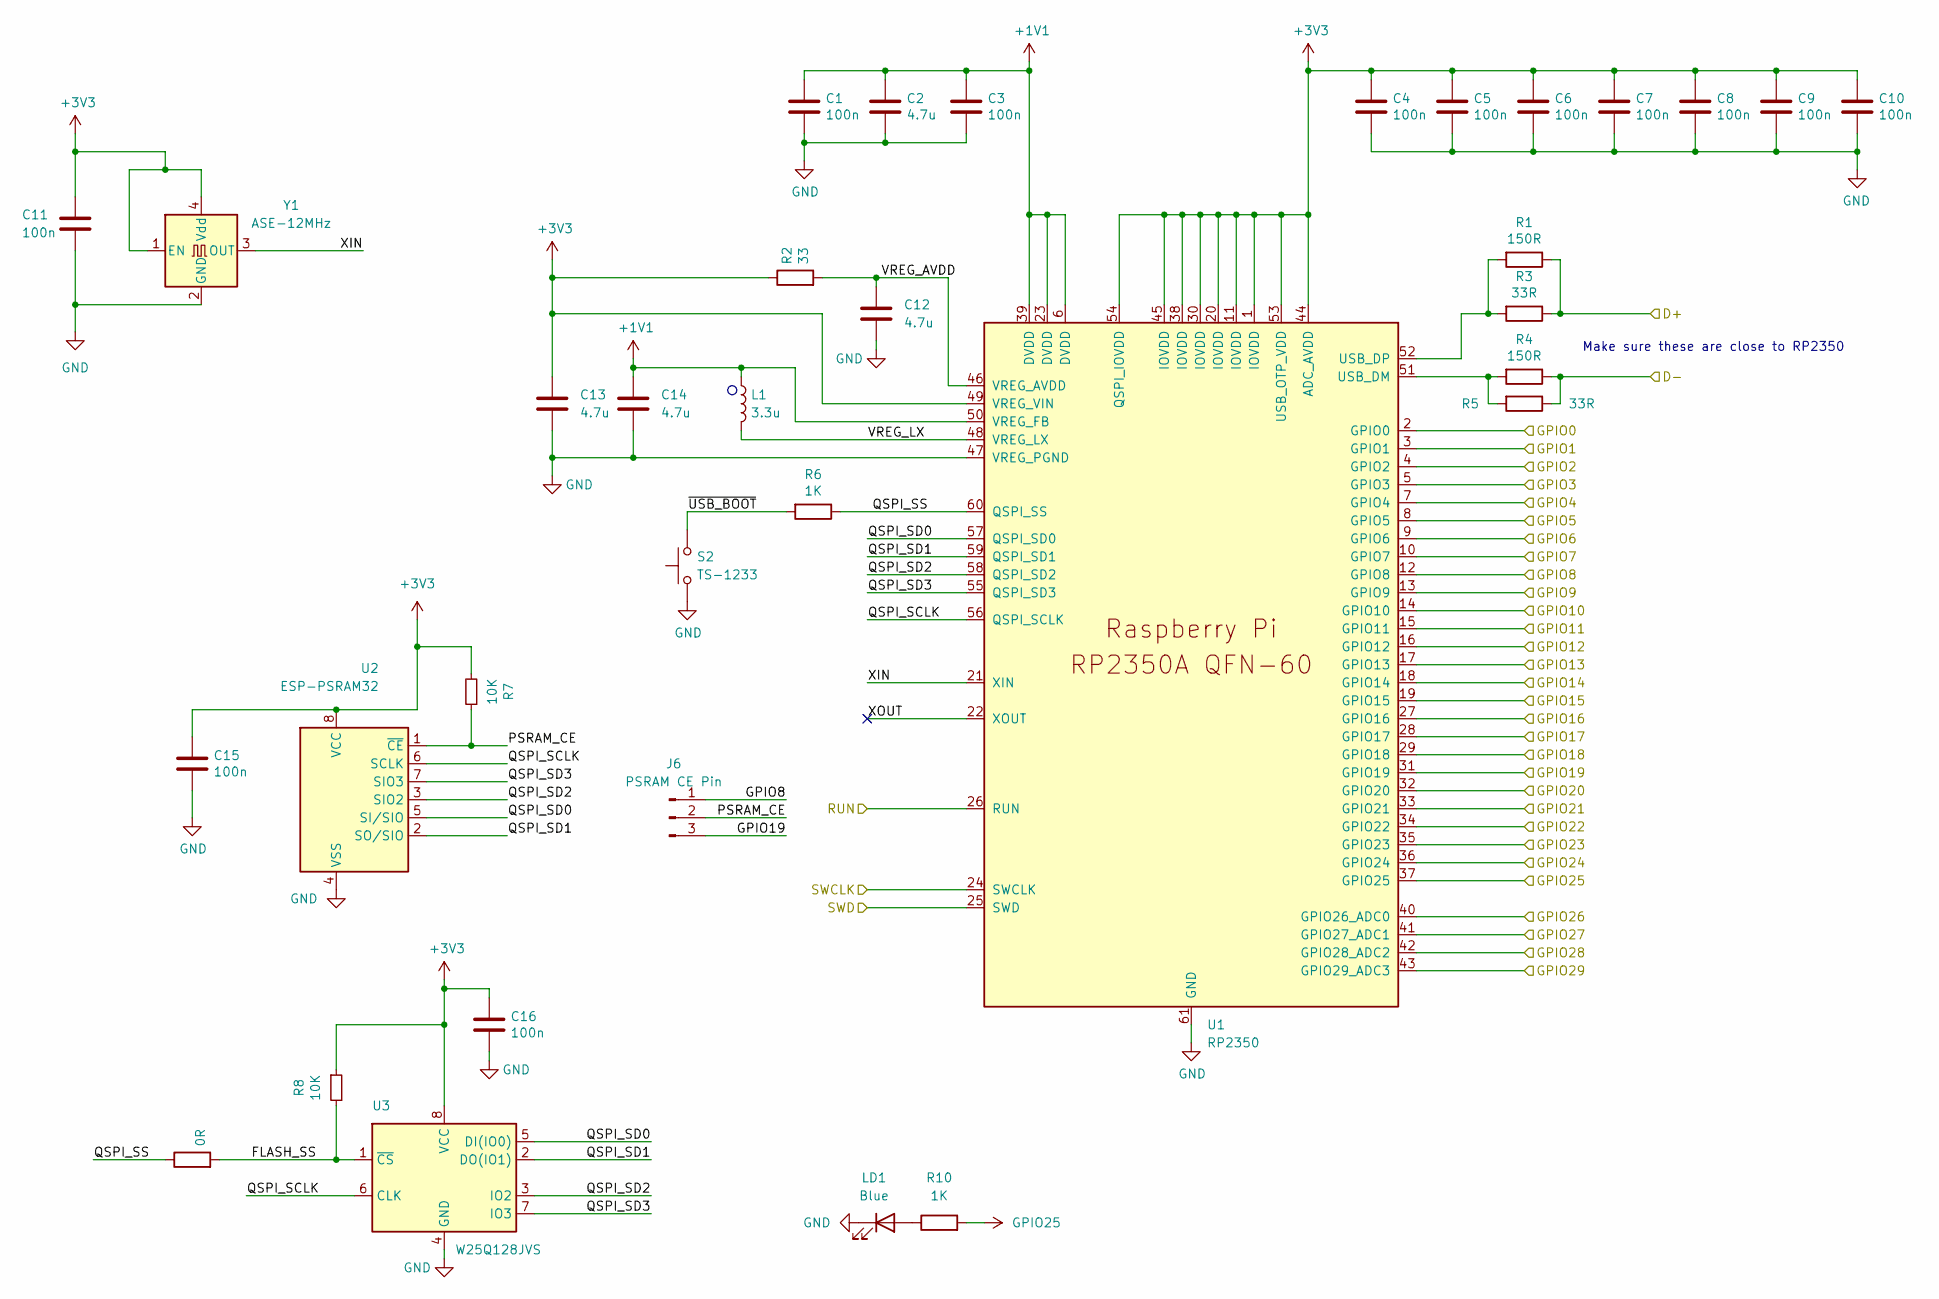
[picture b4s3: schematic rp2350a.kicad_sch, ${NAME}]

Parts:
C1, C3, C4, C5, C6, C7, C8, C9, C10, C11, C15, C16: 100n; Capacitor (0402)
C2, C12, C13, C14: 4.7u; Capacitor (0805)
J6: PSRAM CE Pin; Jumper (solder, 3 pins)
L1: 3.3u; IND_LQH2MCN100K02L
LD1: Blue; LED (0402)
R1, R4: 150R; Resistor (0402)
R2: 33; Resistor (0402)
R3, R5: 33R; Resistor (0402)
R6, R10: 1K; Resistor (0402)
R7, R8: 10K; Resistor (0402)
R9: 0R; Resistor (0402)
S2: TS-1233; Button (SMD, 3x3mm, 1-1)
U1: RP2350; QFN 60 (RP2350A)
U2: ESP-PSRAM32; SO-8
U3: W25Q128JVS; SOIC-8
Y1: ASE-12MHz; Crystal (3225, active)

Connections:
+1V1: C1.1, C2.1, C3.1, C14.1, L1.1, U1.6 (DVDD), U1.23 (DVDD), U1.39 (DVDD), U1.50 (VREG_FB)
+3V3: C4.1, C5.1, C6.1, C7.1, C8.1, C9.1, C10.1, C11.1, C13.1, C15.1, C16.1, R2.1, R7.2, R8.1, U1.1 (IOVDD), U1.11 (IOVDD), U1.20 (IOVDD), U1.30 (IOVDD), U1.38 (IOVDD), U1.44 (ADC_AVDD), U1.45 (IOVDD), U1.49 (VREG_VIN), U1.53 (USB_OTP_VDD), U1.54 (QSPI_IOVDD), U2.8 (VCC), U3.8 (VCC), Y1.1 (EN), Y1.4 (Vdd); also elsewhere on the board
/D+: R1.1, R3.1; also elsewhere on the board
/D-: R4.1, R5.1; also elsewhere on the board
/GPIO0: U1.2 (GPIO0); also elsewhere on the board
/GPIO1: U1.3 (GPIO1); also elsewhere on the board
/GPIO2: U1.4 (GPIO2); also elsewhere on the board
/GPIO3: U1.5 (GPIO3); also elsewhere on the board
/GPIO4: U1.7 (GPIO4); also elsewhere on the board
/GPIO5: U1.8 (GPIO5); also elsewhere on the board
/GPIO6: U1.9 (GPIO6); also elsewhere on the board
/GPIO7: U1.10 (GPIO7); also elsewhere on the board
/GPIO8: J6.1, U1.12 (GPIO8); also elsewhere on the board
/GPIO9: U1.13 (GPIO9); also elsewhere on the board
/GPIO10: U1.14 (GPIO10); also elsewhere on the board
/GPIO11: U1.15 (GPIO11); also elsewhere on the board
/GPIO12: U1.16 (GPIO12); also elsewhere on the board
/GPIO13: U1.17 (GPIO13); also elsewhere on the board
/GPIO14: U1.18 (GPIO14); also elsewhere on the board
/GPIO15: U1.19 (GPIO15); also elsewhere on the board
/GPIO16: U1.27 (GPIO16); also elsewhere on the board
/GPIO17: U1.28 (GPIO17); also elsewhere on the board
/GPIO18: U1.29 (GPIO18); also elsewhere on the board
/GPIO19: J6.3, U1.31 (GPIO19); also elsewhere on the board
/GPIO20: U1.32 (GPIO20); also elsewhere on the board
/GPIO21: U1.33 (GPIO21); also elsewhere on the board
/GPIO22: U1.34 (GPIO22); also elsewhere on the board
/GPIO23: U1.35 (GPIO23); also elsewhere on the board
/GPIO24: U1.36 (GPIO24); also elsewhere on the board
/GPIO26: U1.40 (GPIO26_ADC0); also elsewhere on the board
/GPIO27: U1.41 (GPIO27_ADC1); also elsewhere on the board
/GPIO28: U1.42 (GPIO28_ADC2); also elsewhere on the board
/GPIO29: U1.43 (GPIO29_ADC3); also elsewhere on the board
/RP2350A/FLASH_SS: R8.2, R9.2, U3.1 (~CS)
/RP2350A/PSRAM_CE: J6.2, R7.1, U2.1 (~CE)
/RP2350A/QSPI_SCLK: U1.56 (QSPI_SCLK), U2.6 (SCLK), U3.6 (CLK)
/RP2350A/QSPI_SD0: U1.57 (QSPI_SD0), U2.5 (SI/SIO), U3.5 (DI(IO0))
/RP2350A/QSPI_SD1: U1.59 (QSPI_SD1), U2.2 (SO/SIO), U3.2 (DO(IO1))
/RP2350A/QSPI_SD2: U1.58 (QSPI_SD2), U2.3 (SIO2), U3.3 (IO2)
/RP2350A/QSPI_SD3: U1.55 (QSPI_SD3), U2.7 (SIO3), U3.7 (IO3)
/RP2350A/QSPI_SS: R6.1, R9.1, U1.60 (QSPI_SS)
/RP2350A/VREG_AVDD: C12.1, R2.2, U1.46 (VREG_AVDD)
/RP2350A/VREG_LX: L1.2, U1.48 (VREG_LX)
/RP2350A/XIN: U1.21 (XIN), Y1.3 (OUT)
/RP2350A/XOUT: U1.22 (XOUT)
/RP2350A/~USB_BOOT: R6.2, S2.2
/RUN: U1.26 (RUN); also elsewhere on the board
/SWCLK: U1.24 (SWCLK)
/SWD: U1.25 (SWD)
GND: C1.2, C2.2, C3.2, C4.2, C5.2, C6.2, C7.2, C8.2, C9.2, C10.2, C11.2, C12.2, C13.2, C14.2, C15.2, C16.2, LD1.1 (K), S2.1, U1.47 (VREG_PGND), U1.61 (GND), U2.4 (VSS), U3.4 (GND), Y1.2 (GND); also elsewhere on the board
GPIO25: R10.2, U1.37 (GPIO25); also elsewhere on the board
unnamed: LD1.2 (A), R10.1
unnamed: R4.2, R5.2, U1.51 (USB_DM)
unnamed: R1.2, R3.2, U1.52 (USB_DP)

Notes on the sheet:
Make sure these are close to RP2350

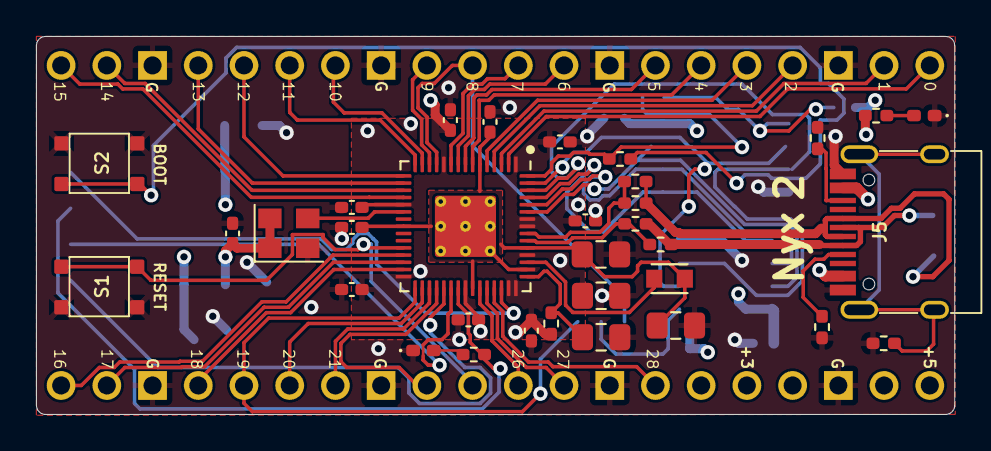
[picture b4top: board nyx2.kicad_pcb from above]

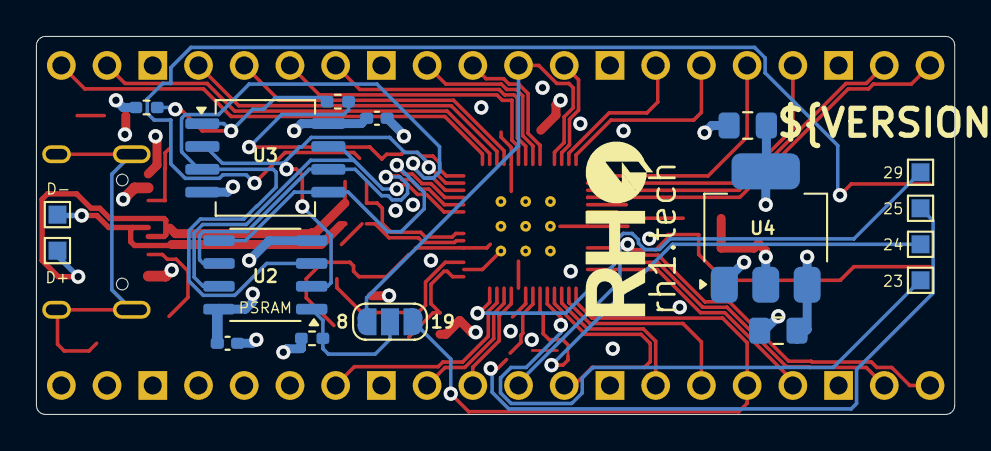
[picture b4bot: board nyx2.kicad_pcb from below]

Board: 4 copper layers, 51.0 x 21.0 mm, 48 parts (13 on the bottom side), 56 nets.
